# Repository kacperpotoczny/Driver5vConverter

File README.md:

# Converter for Beckhoff step motor driver for motors with 5V output
It helps to read the Home signals from motoros like NSA 12 or other with optical Home/END position sensors

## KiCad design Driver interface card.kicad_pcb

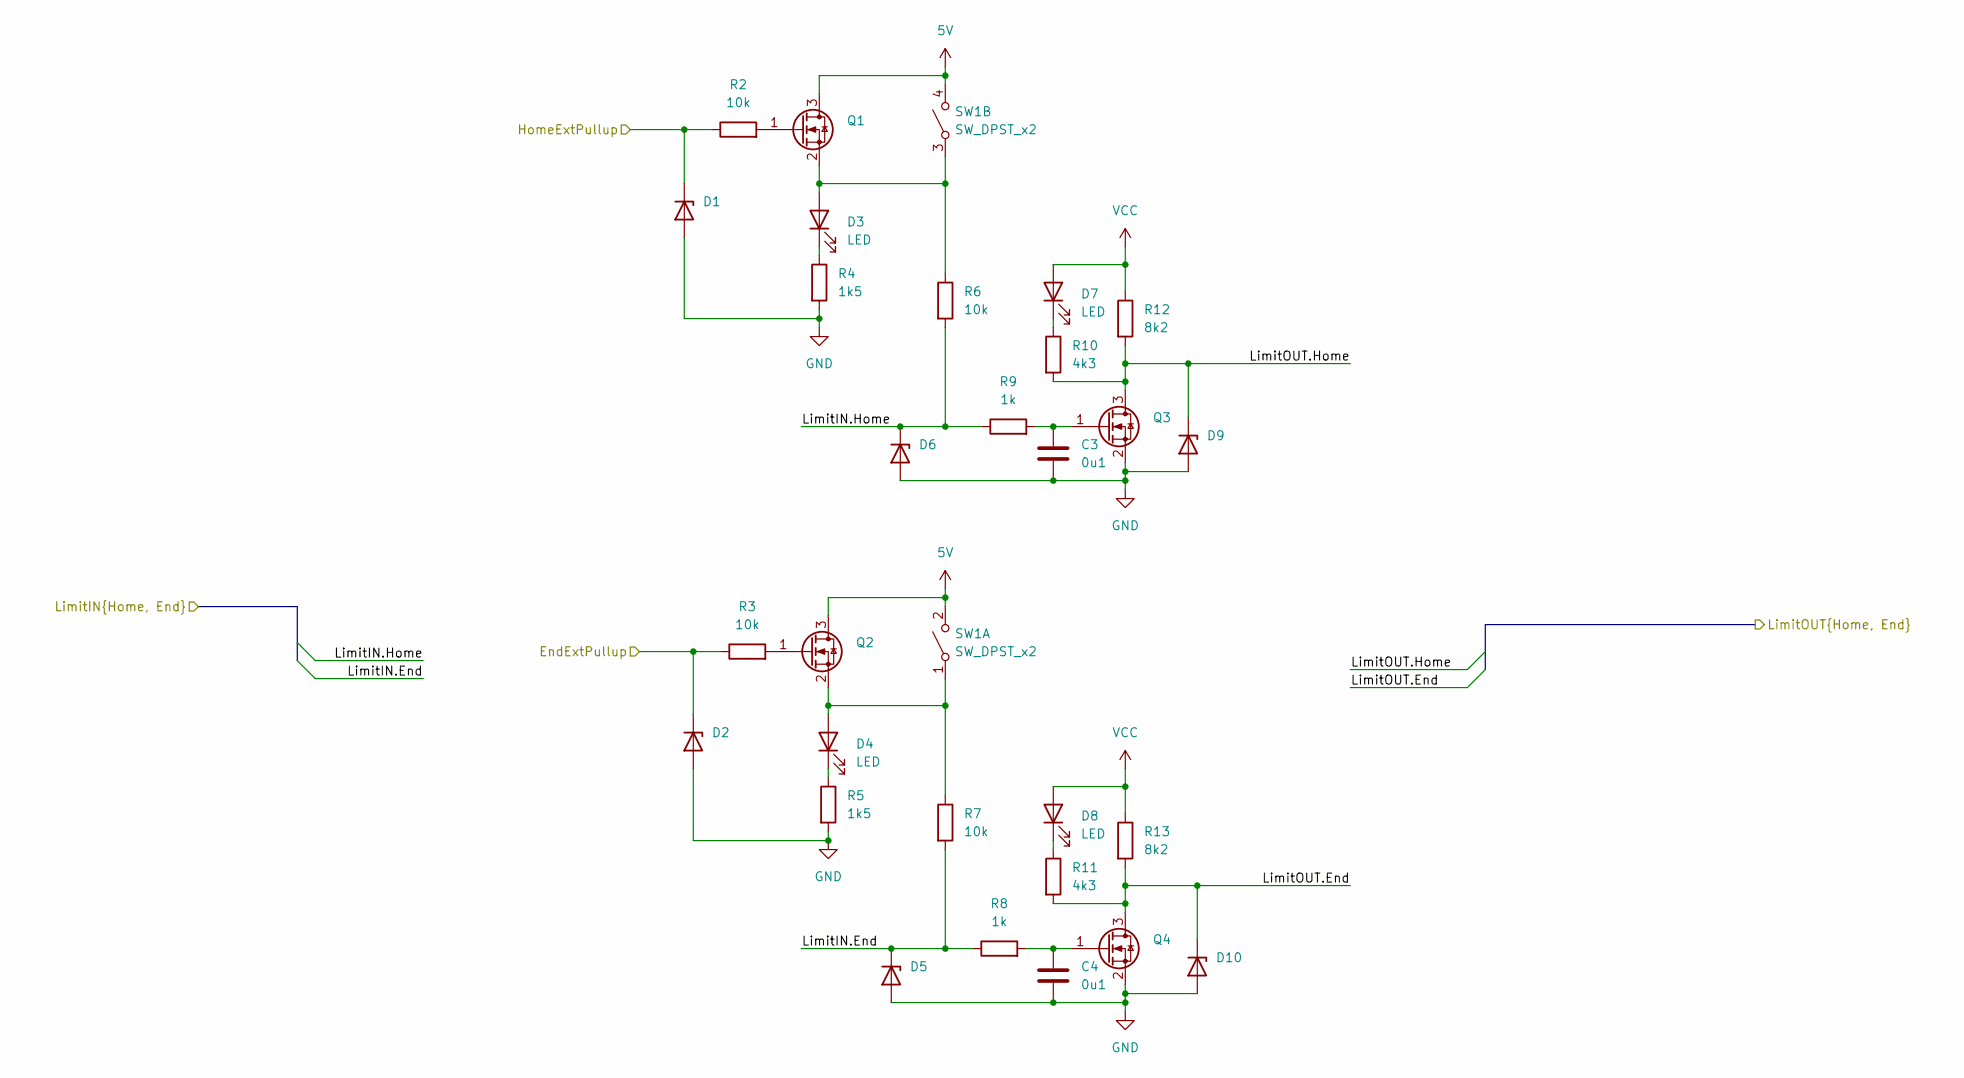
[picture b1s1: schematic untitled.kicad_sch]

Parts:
C3, C4: 0u1; C_0603_1608Metric_Pad1.08x0.95mm_HandSolder
D1, D2, D5, D6, D9, D10: PTVS26VZ1USK; Nexperia_DSN1608-2_1.6x0.8mm
D3, D4, D7, D8: LED; LED_0603_1608Metric_Pad1.05x0.95mm_HandSolder
Q1, Q2, Q3, Q4: 2N7002H; SOT-23
R2, R3, R6, R7: 10k; R_0603_1608Metric_Pad0.98x0.95mm_HandSolder
R4, R5: 1k5; R_0603_1608Metric_Pad0.98x0.95mm_HandSolder
R8, R9: 1k; R_0603_1608Metric_Pad0.98x0.95mm_HandSolder
R10, R11: 4k3; R_0603_1608Metric_Pad0.98x0.95mm_HandSolder
R12, R13: 8k2; R_0603_1608Metric_Pad0.98x0.95mm_HandSolder
SW1: SW_DPST_x2; SW_DIP_SPSTx02_Slide_6.7x6.64mm_W6.73mm_P2.54mm_LowProfile_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

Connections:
5V: Q1.3 (D), Q2.3 (D), SW1.2 (B), SW1.4 (B); also elsewhere on the board
/Driver connector/End1Pullup: D2.1 (K), R3.1; also elsewhere on the board
/Driver connector/Home1Pullup: D1.1 (K), R2.1; also elsewhere on the board
/Driver connector/LimitOUT1.End: D10.1 (K), Q4.3 (D), R11.2, R13.2; also elsewhere on the board
/Driver connector/LimitOUT1.Home: D9.1 (K), Q3.3 (D), R10.2, R12.2; also elsewhere on the board
/Logic converter/LimitIN.End: D5.1 (K), R7.2, R8.1; also elsewhere on the board
/Logic converter/LimitIN.Home: D6.1 (K), R6.2, R9.1; also elsewhere on the board
GND: C3.2, C4.2, D1.2 (A), D2.2 (A), D5.2 (A), D6.2 (A), D9.2 (A), D10.2 (A), Q3.2 (S), Q4.2 (S), R4.2, R5.2; also elsewhere on the board
unnamed: D3.2 (A), Q1.2 (S), R6.1, SW1.3 (A)
unnamed: D3.1 (K), R4.1
unnamed: D4.2 (A), Q2.2 (S), R7.1, SW1.1 (A)
unnamed: D4.1 (K), R5.1
unnamed: D7.1 (K), R10.1
unnamed: D8.1 (K), R11.1
unnamed: Q1.1 (G), R2.2
unnamed: Q2.1 (G), R3.2
unnamed: C3.1, Q3.1 (G), R9.2
unnamed: C4.1, Q4.1 (G), R8.2
VCC: D7.2 (A), D8.2 (A), R12.1, R13.1; also elsewhere on the board

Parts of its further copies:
C5, C6: 0u1; C_0603_1608Metric_Pad1.08x0.95mm_HandSolder
D11, D12, D15, D16, D19, D20: PTVS26VZ1USK; Nexperia_DSN1608-2_1.6x0.8mm
D13, D14, D17, D18: LED; LED_0603_1608Metric_Pad1.05x0.95mm_HandSolder
Q5, Q6, Q7, Q8: 2N7002H; SOT-23
R15, R16, R19, R20: 10k; R_0603_1608Metric_Pad0.98x0.95mm_HandSolder
R17, R18: 1k5; R_0603_1608Metric_Pad0.98x0.95mm_HandSolder
R21, R22: 1k; R_0603_1608Metric_Pad0.98x0.95mm_HandSolder
R23, R24: 4k3; R_0603_1608Metric_Pad0.98x0.95mm_HandSolder
R25, R26: 8k2; R_0603_1608Metric_Pad0.98x0.95mm_HandSolder
SW2: SW_DPST_x2; SW_DIP_SPSTx02_Slide_6.7x6.64mm_W6.73mm_P2.54mm_LowProfile_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

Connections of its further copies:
5V: Q5.3 (D), Q6.3 (D), SW2.2 (B), SW2.4 (B); also elsewhere on the board
/Driver connector/End2Pullup: D12.1 (K), R16.1; also elsewhere on the board
/Driver connector/Home2Pullup: D11.1 (K), R15.1; also elsewhere on the board
/Driver connector/LimitOUT2.End: D20.1 (K), Q8.3 (D), R24.2, R26.2; also elsewhere on the board
/Driver connector/LimitOUT2.Home: D19.1 (K), Q7.3 (D), R23.2, R25.2; also elsewhere on the board
/Logic converter1/LimitIN.End: D15.1 (K), R20.2, R21.1; also elsewhere on the board
/Logic converter1/LimitIN.Home: D16.1 (K), R19.2, R22.1; also elsewhere on the board
GND: C5.2, C6.2, D11.2 (A), D12.2 (A), D15.2 (A), D16.2 (A), D19.2 (A), D20.2 (A), Q7.2 (S), Q8.2 (S), R17.2, R18.2; also elsewhere on the board
unnamed: D13.2 (A), Q5.2 (S), R19.1, SW2.3 (A)
unnamed: D13.1 (K), R17.1
unnamed: D14.2 (A), Q6.2 (S), R20.1, SW2.1 (A)
unnamed: D14.1 (K), R18.1
unnamed: D17.1 (K), R23.1
unnamed: D18.1 (K), R24.1
unnamed: Q5.1 (G), R15.2
unnamed: Q6.1 (G), R16.2
unnamed: C5.1, Q7.1 (G), R22.2
unnamed: C6.1, Q8.1 (G), R21.2
VCC: D17.2 (A), D18.2 (A), R25.1, R26.1; also elsewhere on the board

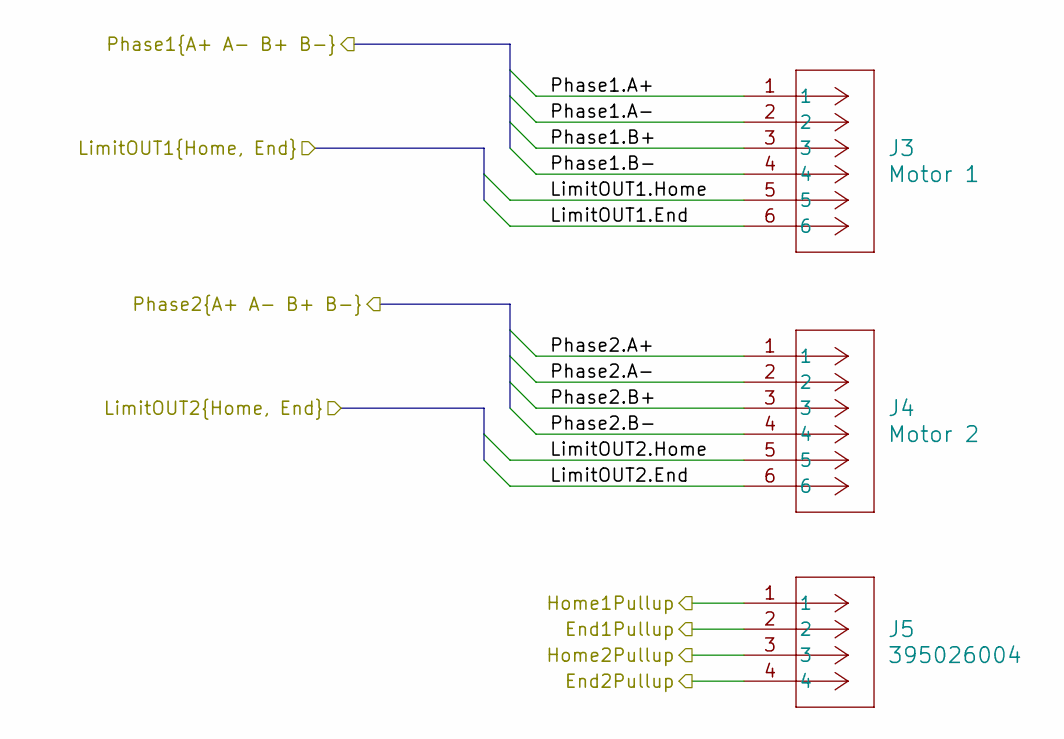
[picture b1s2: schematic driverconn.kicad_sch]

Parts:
J3: Motor 1; CONN_SD-39502-001_06P_MOL
J4: Motor 2; CONN_SD-39502-001_06P_MOL
J5: 395026004; CONN_SD-39502-001_04P_MOL

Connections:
/Driver connector/End1Pullup: J5.2; also elsewhere on the board
/Driver connector/End2Pullup: J5.4; also elsewhere on the board
/Driver connector/Home1Pullup: J5.1; also elsewhere on the board
/Driver connector/Home2Pullup: J5.3; also elsewhere on the board
/Driver connector/LimitOUT1.End: J3.6; also elsewhere on the board
/Driver connector/LimitOUT1.Home: J3.5; also elsewhere on the board
/Driver connector/LimitOUT2.End: J4.6; also elsewhere on the board
/Driver connector/LimitOUT2.Home: J4.5; also elsewhere on the board
/Driver connector/Phase1.A+: J3.1; also elsewhere on the board
/Driver connector/Phase1.A-: J3.2; also elsewhere on the board
/Driver connector/Phase1.B+: J3.3; also elsewhere on the board
/Driver connector/Phase1.B-: J3.4; also elsewhere on the board
/Driver connector/Phase2.A+: J4.1; also elsewhere on the board
/Driver connector/Phase2.A-: J4.2; also elsewhere on the board
/Driver connector/Phase2.B+: J4.3; also elsewhere on the board
/Driver connector/Phase2.B-: J4.4; also elsewhere on the board

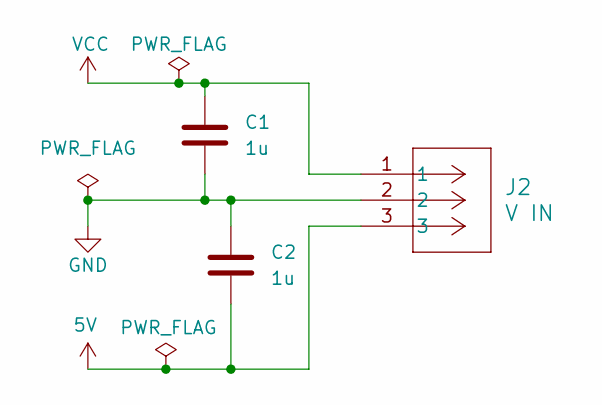
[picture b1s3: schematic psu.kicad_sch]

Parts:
C1, C2: 1u; C_0603_1608Metric_Pad1.08x0.95mm_HandSolder
J2: V IN; CONN_SD-39502-001_03P_MOL

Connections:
5V: C2.2, J2.3; also elsewhere on the board
GND: C1.2, C2.1, J2.2; also elsewhere on the board
VCC: C1.1, J2.1; also elsewhere on the board

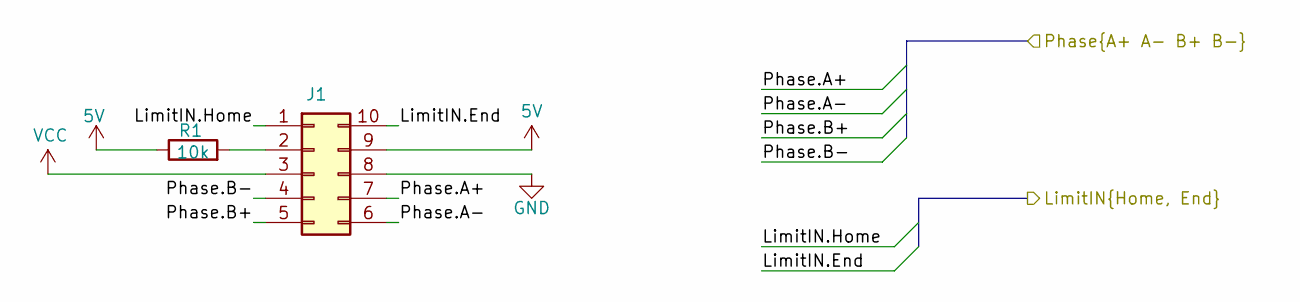
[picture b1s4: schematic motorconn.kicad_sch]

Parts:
J1: Conn_02x05_Counter_Clockwise; DMC 1,5 5-G1-3,5 P20THR
R1: 10k; R_0603_1608Metric_Pad0.98x0.95mm_HandSolder

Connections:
5V: J1.9, R1.1; also elsewhere on the board
/Driver connector/Phase1.A+: J1.7; also elsewhere on the board
/Driver connector/Phase1.A-: J1.6; also elsewhere on the board
/Driver connector/Phase1.B+: J1.5; also elsewhere on the board
/Driver connector/Phase1.B-: J1.4; also elsewhere on the board
/Logic converter/LimitIN.End: J1.10; also elsewhere on the board
/Logic converter/LimitIN.Home: J1.1; also elsewhere on the board
GND: J1.8; also elsewhere on the board
unnamed: J1.2, R1.2
VCC: J1.3; also elsewhere on the board

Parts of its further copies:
J6: Conn_02x05_Counter_Clockwise; DMC 1,5 5-G1-3,5 P20THR
R14: 10k; R_0603_1608Metric_Pad0.98x0.95mm_HandSolder

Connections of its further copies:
5V: J6.9, R14.1; also elsewhere on the board
/Driver connector/Phase2.A+: J6.7; also elsewhere on the board
/Driver connector/Phase2.A-: J6.6; also elsewhere on the board
/Driver connector/Phase2.B+: J6.5; also elsewhere on the board
/Driver connector/Phase2.B-: J6.4; also elsewhere on the board
/Logic converter1/LimitIN.End: J6.10; also elsewhere on the board
/Logic converter1/LimitIN.Home: J6.1; also elsewhere on the board
GND: J6.8; also elsewhere on the board
unnamed: J6.2, R14.2
VCC: J6.3; also elsewhere on the board

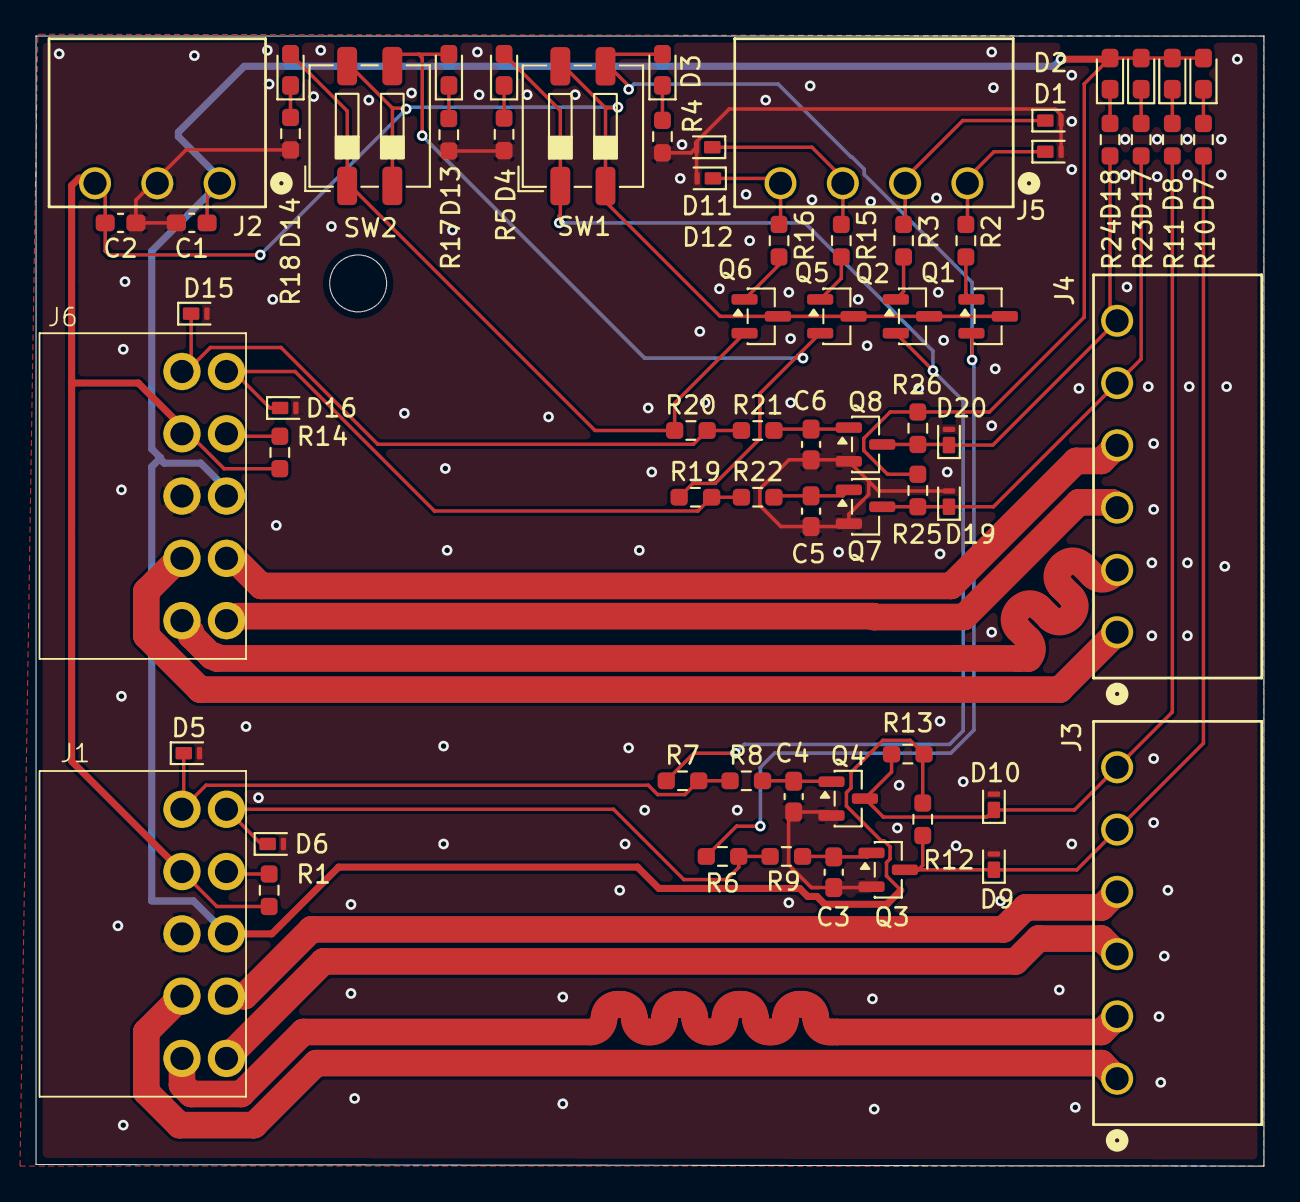
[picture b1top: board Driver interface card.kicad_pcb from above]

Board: 2 copper layers, 69.0 x 63.5 mm, 68 parts (0 on the bottom side), 45 nets.

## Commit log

2026-05-05 first version
2026-06-09 rev2
